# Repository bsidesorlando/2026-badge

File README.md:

# BSides Orlando 2026 Badge

The electronic badge for BSides Orlando 2026, themed around retro-futurism:
a 1960s World's Fair vision of tomorrow, with Lil Chompy the alligator at
the wheel of a flying car.

- **CH32V003** RISC-V microcontroller, powered by one AAA cell through a
  TPS61021A boost converter.
- **Three SK6812MINI-E RGB LEDs:** the flying car's headlights, and the
  fingerprint scanner indicator.
- **Four self-blinking LEDs:** the tower spire and the geodesic sphere.
- **Two capacitive touch pads:** the fingerprint, and Lil Chompy's head.
- **SAO connector:** the badge is an SAOv3 host on I2C, and GPIO1/GPIO2 carry
  a 115200-baud serial console.
- **Serial console:** runs "Lil Chompy and the World's Fair", a small text
  adventure that doubles as a CTF challenge.

> **Spoilers:** the firmware source contains the CTF solutions and flags.

## Repo layout

| Path | Contents |
| --- | --- |
| `hardware/` | KiCad project (`bsidesorl-v1`), symbol and footprint libraries, and artwork sources |
| `hardware/EasyEDA_Gerber_bsidesorl-v1_2026-08-31.zip` | Gerbers as ordered from JLCPCB |
| `hardware/jlcpcb/` | BOM and CPL as ordered from JLCPCB |
| `hardware/mk_easyeda.py` | Writes an EasyEDA Pro-importable copy of the board |
| `firmware/` | Badge firmware (PlatformIO + [ch32fun](https://github.com/cnlohr/ch32fun)); see [firmware/README.md](firmware/README.md) |

## Firmware quick start

```sh
# saov3-lib's public repo isn't published yet
git submodule update --init

# Build
cd firmware
pio run

# Copy firmware to picorvd-for-badges probe
cp .pio/build/bsorl26/firmware.bin /Volumes/PICORVD/
```

For production, badges are flashed by the standalone programmer build of
[picorvd-for-badges](https://github.com/kjcolley7/picorvd-for-badges)
(an RP2040 probe). It shows up as a USB drive named PICORVD: copy `firmware.bin`
onto it, and set `uart_selftest = 0xB5` in its `CONFIG.TXT` so it triggers the
badge's post-flash self-test over the SWIO pin. Its factory log can be copied
off the same drive as `LOG.CSV`.

## Building your own "programmer SAO"

> Note that in the picture, the SAO connector is connected on G14-H16. The
> traces on the back were cut between G and H to avoid bridging them. The
> SAO connector is oriented so the top is facing downwards in this photo,
> meaning 3V3 is on G16 and GND is on H16.

For this, you need a Raspberry Pi Pico or compatible board. I used a
[WaveShare RP2040-Zero](https://www.amazon.com/dp/B0DXL12W59) board for the
production programmer SAOs that were used in the soldering village at
BSides Orlando, since they're smaller and cheaper than a Raspberry Pi Pico.
To use as a standalone programmer (where the programmer receives power from
the connected target badge), only three wires are needed: GND, 3v3, and the
Pico's GP4 -> badge's RXD (aka PD1/SWIO). On this SWIO connection, you should
also attach a 1KΩ pull-up resistor to 3v3. This can easily be done on a
breadboard with jumper wires.

You'll need to build the picorvd-for-badges firmware for the probe. The exact
version used on the programmer SAOs at the conference can be found pre-built
here: https://github.com/bsidesorlando/2026-badge/releases/download/v1.0.0/pico_rvd_factory.uf2

To build it yourself for the WaveShare RP2040-Zero board:

```bash
git clone https://github.com/kjcolley7/picorvd-for-badges.git
cd picorvd-for-badges
cmake -B build-zero -G Ninja -DPICO_BOARD=waveshare_rp2040_zero
ninja -C build-zero pico_rvd_factory
```

The above commands create `build-zero/pico_rvd_factory.uf2`, which should be
uploaded to the probe by putting it in BOOTSEL mode and then copying it to the
USB Mass Storage device it exposes. Then, the probe will reboot into the picorvd
firmware and the USB Mass Storage device will re-appear with the name "PICORVD".
Now, it's ready to accept firmware and configuration. You can upload the BSORL
badge firmware from `.pio/build/bsorl26/firmware.bin` (or the pre-built one from
here: https://github.com/bsidesorlando/2026-badge/releases/download/v1.0.0/firmware.bin)
by copying it into the PICORVD volume (which will disappear and reappear as the
probe reboots), and you can also edit the probe's CONFIG.TXT to add
`uart_selftest = 0xB5` (so the probe tells the BSORL badge to enter selftest mode
after programming). At this point, the probe is fully ready to go, either in
standalone mode or tethered mode.

### Standalone mode

This is the mode that was used at BSides Orlando for programming all of the
attendees' badges in the soldering village. It works by powering the probe board
from the target badge itself, and it immediately attempts to program the
connected target upon boot. The badge needs to be powered on so the probe itself
can be powered.

### Tethered mode

This mode works by leaving the probe connected to a host PC over USB. If you
use pico_rvd.uf2 instead of pico_rvd_factory.uf2, the probe won't automatically
program connected badges. Rather, you'll need to manually issue the `factory`
command to the probe over its UART interface. In the pico_rvd_factory.uf2 build,
it will automatically start in factory mode, ready to program any connected
badges.

**NOTE**: Do NOT connect a probe with USB power to a badge while it is switched
on. The power switch should be in the OFF position before connecting a tethered
probe. The badge and the probe will likely have slightly different values than
exactly 3.3v, so there will be some current leakage. Worst case, it could damage
the AAA battery, causing it to leak.

## Credits

PCB and firmware by Kevin Colley. Art by Shep.

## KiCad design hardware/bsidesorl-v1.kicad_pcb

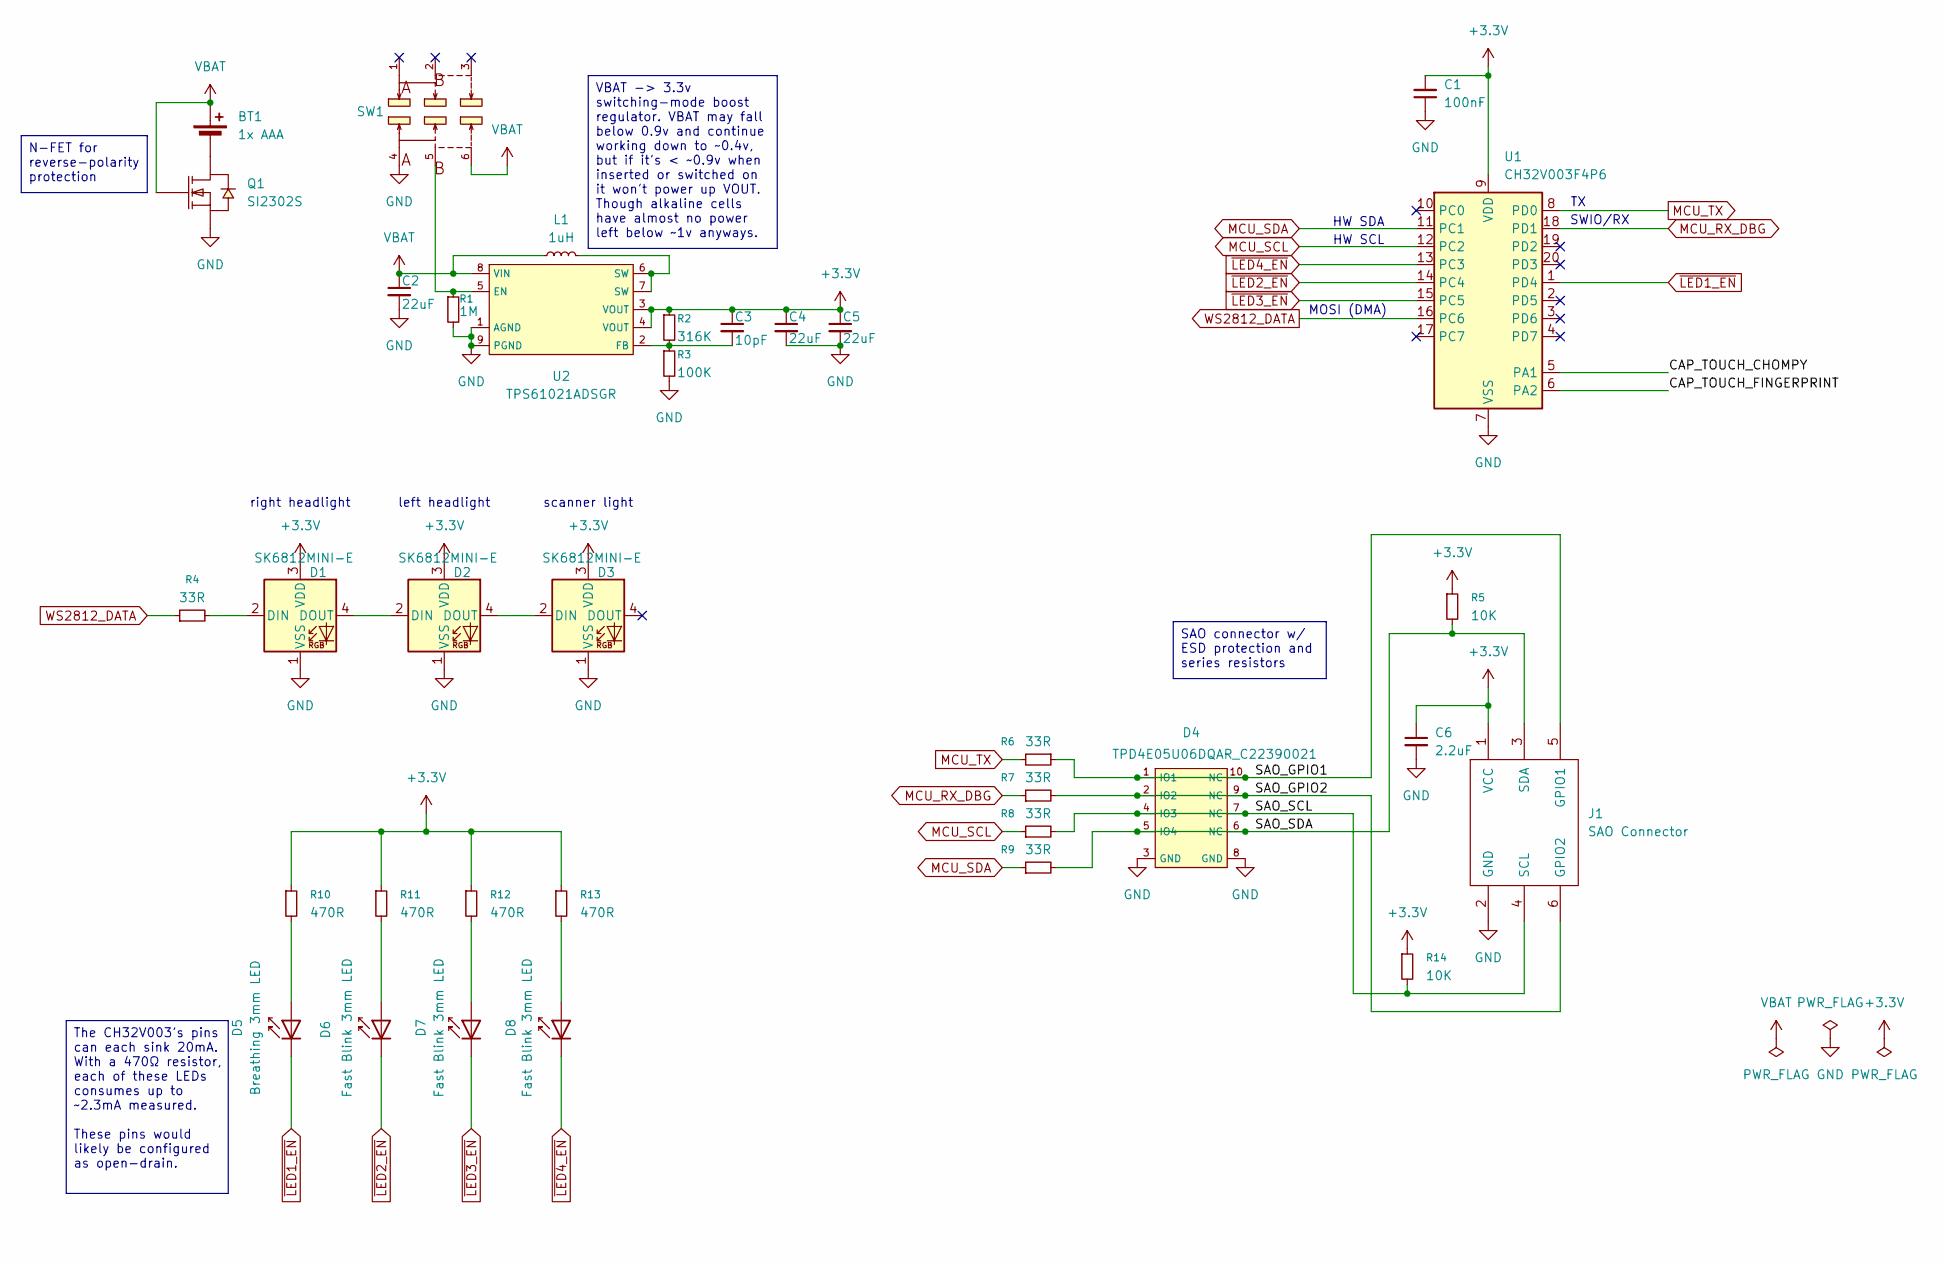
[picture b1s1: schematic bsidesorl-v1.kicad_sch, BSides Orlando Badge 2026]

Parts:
BT1: 1x AAA; BAT-TH_BH-AAA-1X
C1: 100nF; C_0603_1608Metric; LCSC C14663
C2, C4, C5: 22uF; C_0603_1608Metric
C3: 10pF; C_0603_1608Metric
C6: 2.2uF; C_0603_1608Metric; LCSC C23630
D1, D2, D3: SK6812MINI-E; LED_SK6812MINI-E_3.2x2.8mm_P1.5mm_ReverseMount
D4: TPD4E05U06DQAR_C22390021; DFN2510-10_L2.5-W1.0-P0.50-BL; LCSC C22390021
D5: Breathing 3mm LED; LED_D3.0mm_IRBlack
D6, D7, D8: Fast Blink 3mm LED; LED_D3.0mm_IRBlack
J1: SAO Connector; PinSocket_2x03_P2.54mm_Vertical
L1: 1uH; L_1008_2520Metric
Q1: SI2302S; SOT-23-3_L2.9-W1.3-P1.90-LS2.4-BR; LCSC C22463594
R1: 1M; R_0603_1608Metric
R2: 316K; R_0603_1608Metric
R3: 100K; R_0603_1608Metric
R4: 33R; R_0603
R5, R14: 10K; R_0603; LCSC C25804
R6, R7, R8, R9: 33R; R_0603; LCSC C23140
R10, R11, R12, R13: 470R; R_0603_1608Metric; LCSC C23179
SW1: MST22D18G2_125; SW-SMD_MST22D18G2; LCSC C2906280
U1: CH32V003F4P6; TSSOP-20_4.4x6.5mm_P0.65mm; LCSC C5187096
U2: TPS61021ADSGR; WSON-8_L2.0-W2.0-P0.50-TL-EP; LCSC C193037

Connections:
+3.3V: C1.2, C3.1, C4.1, C5.1, C6.1, D1.3 (VDD), D2.3 (VDD), D3.3 (VDD), J1.1 (VCC), R2.1, R5.1, R10.1, R11.1, R12.1, R13.1, R14.1, U1.9 (VDD), U2.3 (VOUT), U2.4 (VOUT)
/CAP_TOUCH_CHOMPY: U1.5 (PA1)
/CAP_TOUCH_FINGERPRINT: U1.6 (PA2)
/SAO_GPIO1: D4.1 (IO1), D4.10 (NC), J1.5 (GPIO1), R6.1
/SAO_GPIO2: D4.2 (IO2), D4.9 (NC), J1.6 (GPIO2), R7.2
/SAO_SCL: D4.4 (IO3), D4.7 (NC), J1.4 (SCL), R8.2, R14.2
/SAO_SDA: D4.5 (IO4), D4.6 (NC), J1.3 (SDA), R5.2, R9.2
GND: C1.1, C2.2, C4.2, C5.2, C6.2, D1.1 (VSS), D2.1 (VSS), D3.1 (VSS), D4.3 (GND), D4.8 (GND), J1.2 (GND), Q1.2 (S), R1.2, R3.2, SW1.4, U1.7 (VSS), U2.1 (AGND), U2.9 (PGND)
MCU_RX_DBG: R7.1, U1.18 (PD1)
MCU_SCL: R8.1, U1.12 (PC2)
MCU_SDA: R9.1, U1.11 (PC1)
MCU_TX: R6.2, U1.8 (PD0)
unnamed: BT1.2 (-), Q1.3 (D)
unnamed: D1.2 (DIN), R4.2
unnamed: D1.4 (DOUT), D2.2 (DIN)
unnamed: D2.4 (DOUT), D3.2 (DIN)
unnamed: D5.2 (A), R10.2
unnamed: D6.2 (A), R11.2
unnamed: D7.2 (A), R12.2
unnamed: D8.2 (A), R13.2
unnamed: L1.2, U2.6 (SW), U2.7 (SW)
unnamed: R1.1, SW1.5, U2.5 (EN)
unnamed: C3.2, R2.2, R3.1, U2.2 (FB)
VBAT: BT1.1 (+), C2.1, L1.1, Q1.1 (G), SW1.6, U2.8 (VIN)
WS2812_DATA: R4.1, U1.16 (PC6)
~LED1_EN: D5.1 (K), U1.1 (PD4)
~LED2_EN: D6.1 (K), U1.14 (PC4)
~LED3_EN: D7.1 (K), U1.15 (PC5)
~LED4_EN: D8.1 (K), U1.13 (PC3)

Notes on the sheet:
left headlight
SWIO/RX
MOSI (DMA)
scanner light
HW SCL
right headlight
HW SDA
VBAT -> 3.3v switching-mode boost regulator. VBAT may fall below 0.9v and continue working down to ~0.4v, but if it's < ~0.9v when inserted or switched on it won't power up VOUT. Though alkaline cells have almost no power left below ~1v anyways.
The CH32V003's pins can each sink 20mA. With a 470Ω resistor, each of these LEDs consumes up to ~2.3mA measured. These pins would likely be configured as open-drain.
SAO connector w/ ESD protection and series resistors
N-FET for reverse-polarity protection

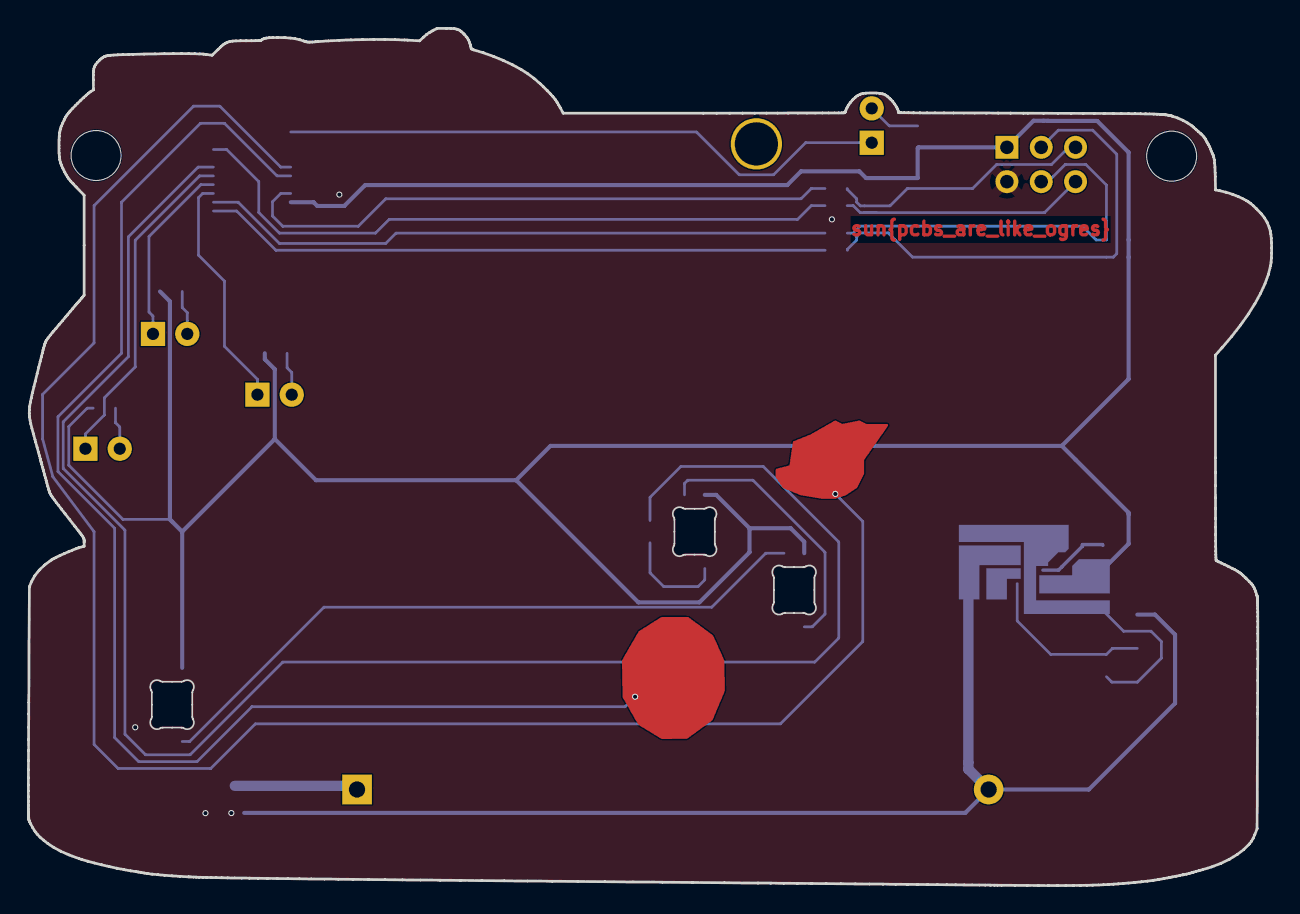
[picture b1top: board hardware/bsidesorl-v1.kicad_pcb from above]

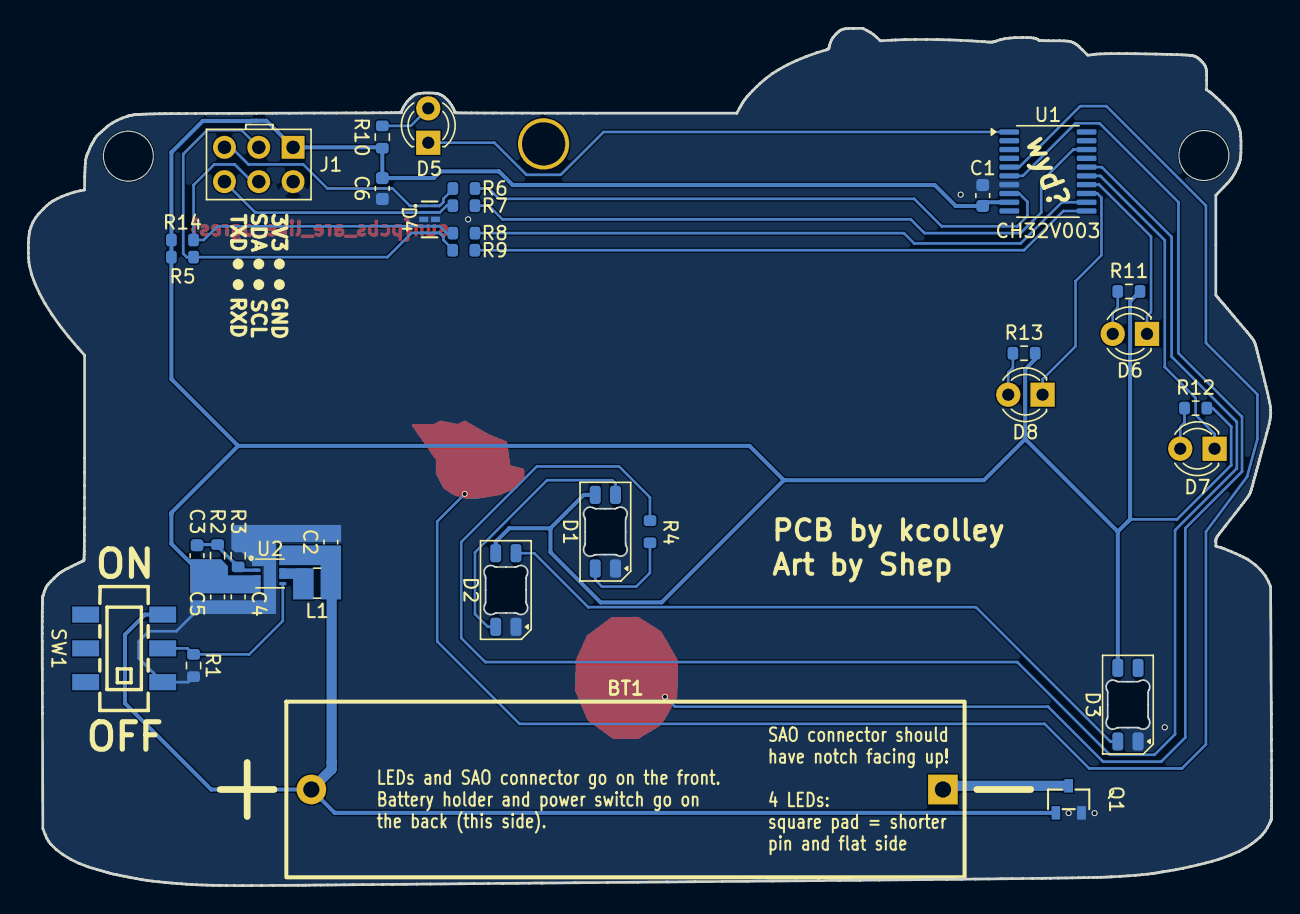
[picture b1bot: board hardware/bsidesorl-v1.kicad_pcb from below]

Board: 2 copper layers, 92.0 x 63.4 mm, 37 parts (30 on the bottom side), 27 nets.

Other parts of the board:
HOLE1, HOLE2: LanyardHole

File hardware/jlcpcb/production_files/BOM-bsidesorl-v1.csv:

Comment,Designator,Footprint,LCSC,Quantity
100K,R3,R_0603_1608Metric,C25803,1
100nF,C1,C_0603_1608Metric,C14663,1
10K,"R14,R5",R_0603,C25804,2
10pF,C3,C_0603_1608Metric,C1634,1
1M,R1,R_0603_1608Metric,C22935,1
1uH,L1,L_1008_2520Metric,C5832356,1
2.2uF,C6,C_0603_1608Metric,C23630,1
22uF,"C2,C4,C5",C_0603_1608Metric,C59461,3
316K,R2,R_0603_1608Metric,C25814,1
33R,"R4,R6,R7,R8,R9",R_0603,C23140,5
470R,"R10,R11,R12,R13",R_0603_1608Metric,C23179,4
CH32V003F4P6,U1,TSSOP-20_4.4x6.5mm_P0.65mm,C5187096,1
SI2302S,Q1,SOT-23-3_L2.9-W1.3-P1.90-LS2.4-BR,C22463594,1
SK6812MINI-E,"D1,D2,D3",LED_SK6812MINI-E_3.2x2.8mm_P1.5mm_ReverseMount,C5149201,3
TPD4E05U06DQAR_C22390021,D4,DFN2510-10_L2.5-W1.0-P0.50-BL,C22390021,1
TPS61021ADSGR,U2,WSON-8_L2.0-W2.0-P0.50-TL-EP,C193037,1

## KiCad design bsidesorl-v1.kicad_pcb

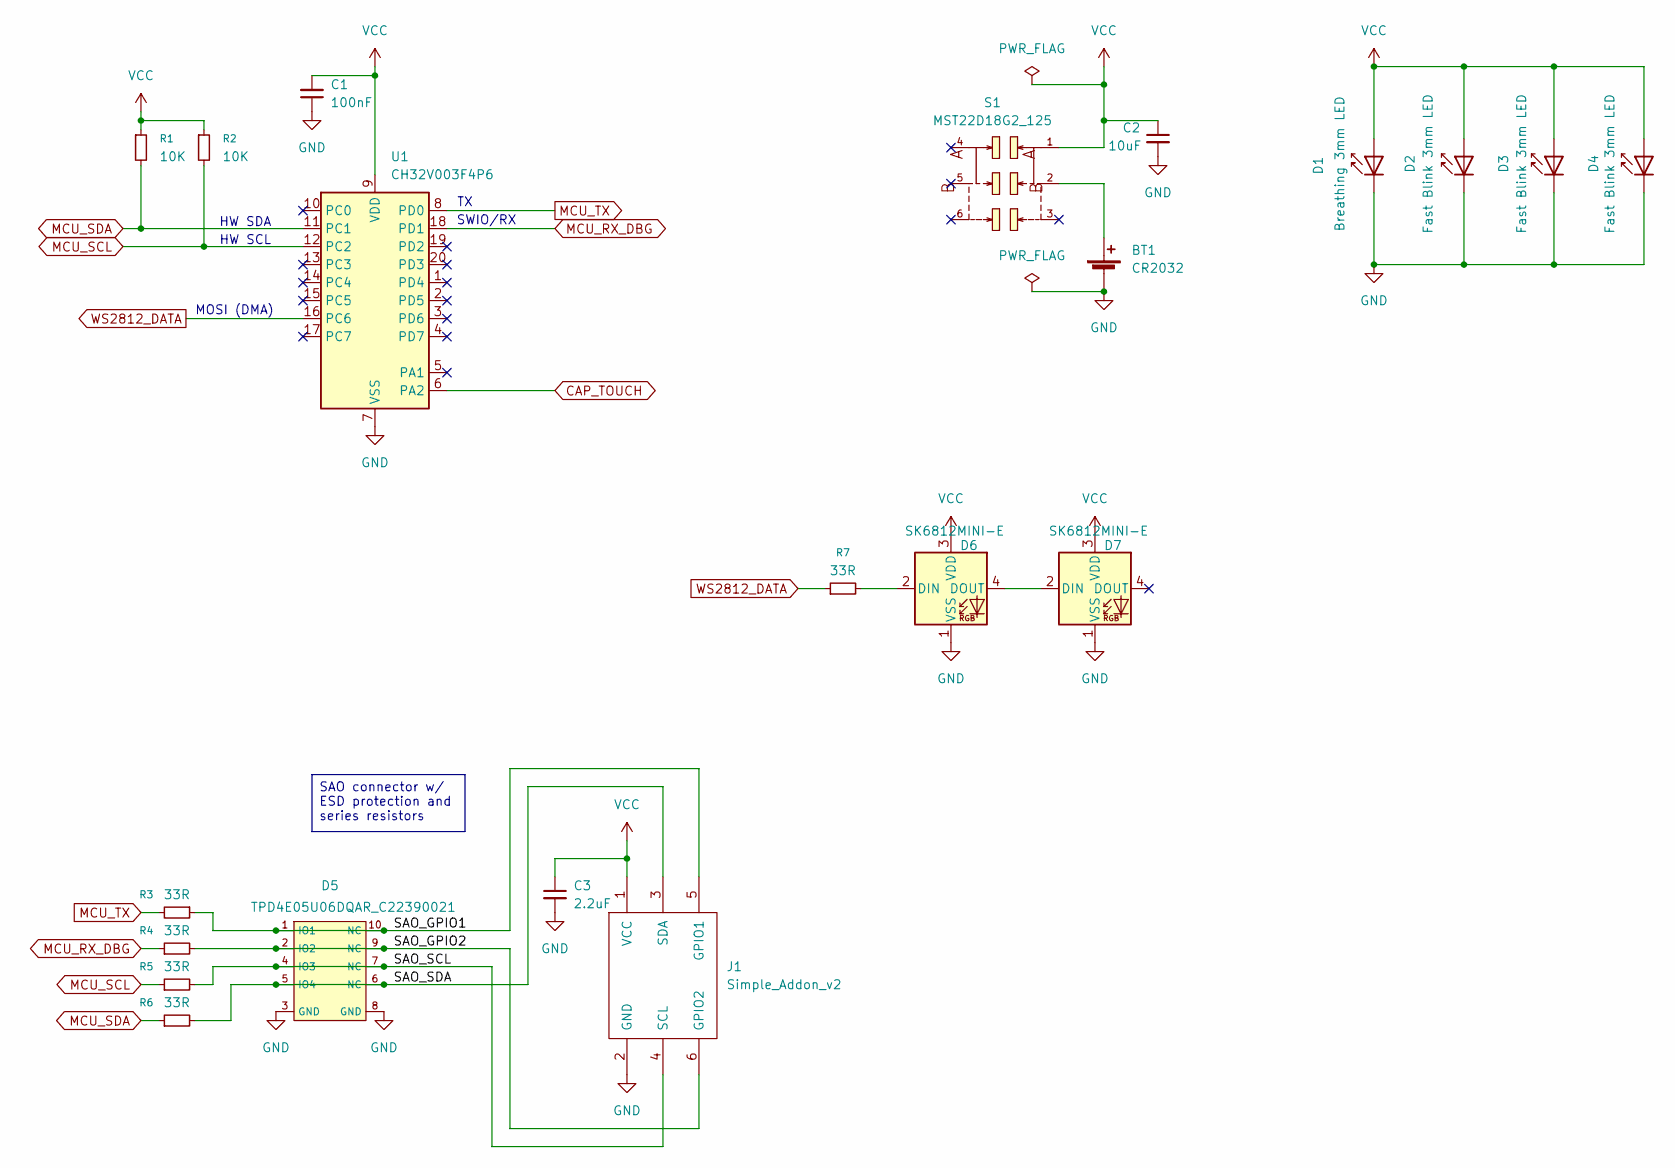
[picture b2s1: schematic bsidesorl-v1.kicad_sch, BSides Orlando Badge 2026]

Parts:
BT1: CR2032; BatteryHolder_Keystone_3002_1x2032
C1: 100nF; C_0603_1608Metric; LCSC C14663
C2: 10uF; C_0603_1608Metric; LCSC C19702
C3: 2.2uF; C_0603_1608Metric; LCSC C23630
D1: Breathing 3mm LED; LED_D3.0mm_IRBlack
D2, D3, D4: Fast Blink 3mm LED; LED_D3.0mm_IRBlack
D5: TPD4E05U06DQAR_C22390021; DFN2510-10_L2.5-W1.0-P0.50-BL; LCSC C22390021
D6, D7: SK6812MINI-E; LED_SK6812MINI-E_3.2x2.8mm_P1.5mm_ReverseMount
J1: Simple_Addon_v2; PinSocket_2x03_P2.54mm_Vertical
R1, R2: 10K; R_0603; LCSC C25804
R3, R4, R5, R6: 33R; R_0603; LCSC C23140
R7: 33R; R_0603
S1: MST22D18G2_125; SW-SMD_MST22D18G2; LCSC C2906280
U1: CH32V003F4P6; TSSOP-20_4.4x6.5mm_P0.65mm; LCSC C5187096

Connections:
/SAO_GPIO1: D5.1 (IO1), D5.10 (NC), J1.5 (GPIO1), R3.1
/SAO_GPIO2: D5.2 (IO2), D5.9 (NC), J1.6 (GPIO2), R4.2
/SAO_SCL: D5.4 (IO3), D5.7 (NC), J1.4 (SCL), R5.2
/SAO_SDA: D5.5 (IO4), D5.6 (NC), J1.3 (SDA), R6.2
CAP_TOUCH: U1.6 (PA2)
GND: BT1.2 (-), C1.1, C2.2, C3.2, D1.1 (K), D2.1 (K), D3.1 (K), D4.1 (K), D5.3 (GND), D5.8 (GND), D6.1 (VSS), D7.1 (VSS), J1.2 (GND), U1.7 (VSS)
MCU_RX_DBG: R4.1, U1.18 (PD1)
MCU_SCL: R2.2, R5.1, U1.12 (PC2)
MCU_SDA: R1.2, R6.1, U1.11 (PC1)
MCU_TX: R3.2, U1.8 (PD0)
unnamed: BT1.1 (+), S1.2
unnamed: D6.2 (DIN), R7.2
unnamed: D6.4 (DOUT), D7.2 (DIN)
VCC: C1.2, C2.1, C3.1, D1.2 (A), D2.2 (A), D3.2 (A), D4.2 (A), D6.3 (VDD), D7.3 (VDD), J1.1 (VCC), R1.1, R2.1, S1.1, U1.9 (VDD)
WS2812_DATA: R7.1, U1.16 (PC6)

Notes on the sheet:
SWIO/RX
MOSI (DMA)
HW SCL
HW SDA
SAO connector w/ ESD protection and series resistors

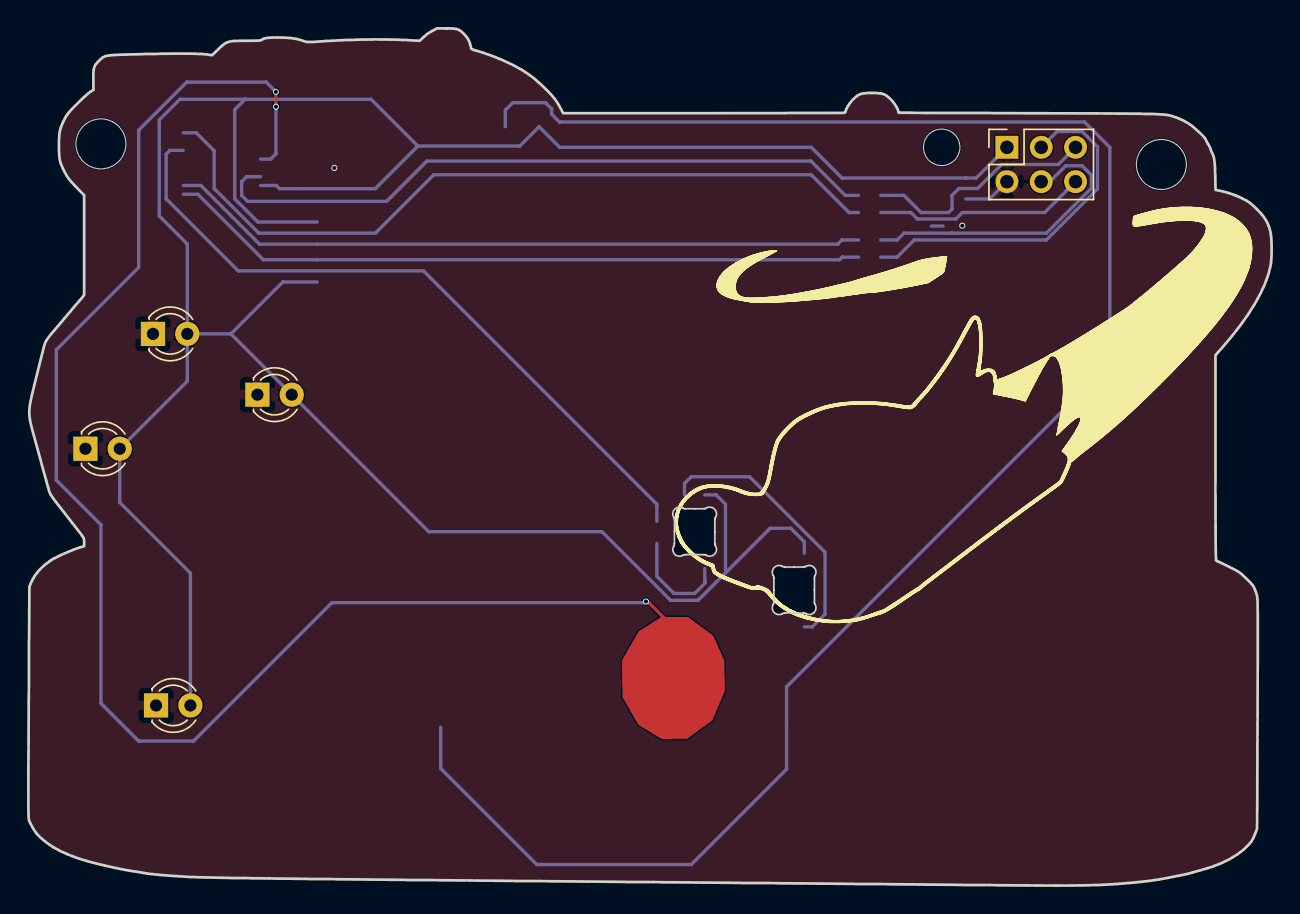
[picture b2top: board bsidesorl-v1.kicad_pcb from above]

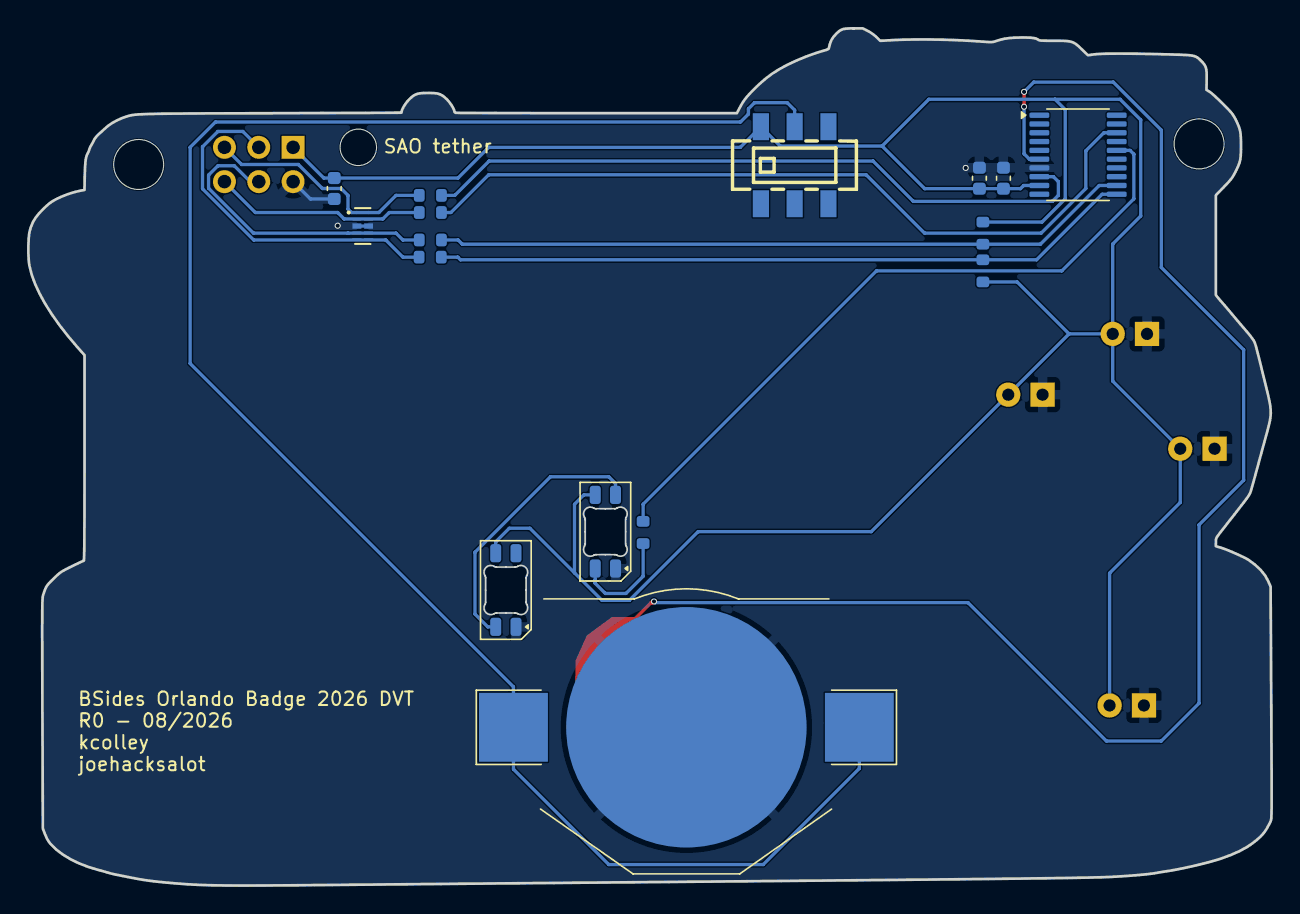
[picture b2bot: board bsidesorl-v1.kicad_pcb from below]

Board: 2 copper layers, 92.0 x 63.4 mm, 21 parts (16 on the bottom side), 14 nets.

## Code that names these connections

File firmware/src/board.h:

#ifndef _BOARD_H
#define _BOARD_H

// Pin map for the production (R1) PCB. See hardware/bsidesorl-v1.kicad_sch.

// SK6812MINI-E chain on PC6 (SPI1 MOSI, streamed by DMA1 channel 3). Chain
// order is D1 -> D2 -> D3.
#define RGB_HEADLIGHT_L 0    // D1, flying car headlight (left, facing the badge)
#define RGB_HEADLIGHT_R 1    // D2, flying car headlight (right)
#define RGB_SCANNER     2    // D3, the "SCANNING IN PROGRESS" indicator
#define RGB_COUNT       3

// Self-blinking 3mm LEDs. Each MCU pin sits in the LED's ground return path,
// so these are open drain: pull low to light, release to turn off.
#define PIN_SPIRE   PD4      // D5, breathing LED at the top of the tower spire
// D6-D8, fast-blink LEDs on the geodesic sphere:
#define PIN_SPHERE0 PC4      // D6
#define PIN_SPHERE1 PC5      // D7
#define PIN_SPHERE2 PC3      // D8

// Capacitive touch pads (ADC slope sensing).
#define TOUCH_FINGERPRINT_PIN 2    // PA2, ADC channel 0
#define TOUCH_FINGERPRINT_ADC 0
#define TOUCH_CHOMPY_PIN      1    // PA1, ADC channel 1 (Lil Chompy's head)
#define TOUCH_CHOMPY_ADC      1

// SAO connector:
//   PC1/PC2 -> SDA/SCL (badge is the SMBus master)
//   PD0 -> GPIO1, doubles as the console's UART TX (USART1 partial remap 1)
//   PD1 -> GPIO2, doubles as the console's UART RX -- and is SWIO (debug)

#endif
